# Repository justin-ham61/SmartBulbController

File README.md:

# SmartBulbController
SmartBulbController is an open-source input device built for the ESP32 microcontroller for controlling Smart Bulbs using the TP-Link Smart Home Protocol.

The goal of this project was to create a remote control device for Kasa Smart Lighting system within local network in order to eliminate the need for a smart phone app for lighting control.

# Dependencies
Several libraries are required for the device to work. 
- Adafruit_SSD1306 by Adafruit
- Adafruit_BusIO by Adafruit
- Adafruit_GFX_Library by Adafruit
- Ai_Esp32_Rotary_Encoder by Igor Antolic
- KasaSmartPlug updated by Justin Ham
    - Modified version of the [KasaSmartPlug](https://github.com/kj831ca/KasaSmartPlug?tab=readme-ov-file) library by Kris Jearakul to be compatible with Smart Bulbs and Smart Plugs.
- ArduinoJson by Benoit Blanchon

# Features
- Quick communication with light bulbs using the TP-Link Smart Home Protocol which is a TCP/IP Protocol that sends JSON payloads to devices. 
- Rotary Knob allows the control of brightness for multiple bulbs at the same time which is not available in the Kasa app.
- Built on FreeRTOS for efficient and responsive device interaction.
- OLED Display for bulb management and view of device states such as (On, Off, Error).

# FreeRTOS
- WiFi related tasks are managed using Semaphores and prohibits reliant tasks from running unless a connection is successfully made.
- User inputs are handled with ISR's that interact with RTOS queues.
- All tasks only operate when items are added to the queue and executes them promptly.
- Tasks notify lower priority tasks such as display task in order to update display.

# Designs

## Device Render
Device was designed with Fusion and prototype was printed using an Ender 3 Pro 3D Printer.

## First Working Prototype
First working prototype of the controller with a custom PCB and the 3D printed case.

## OLED Display
- Menu
    - List of all bulbs and a dedicated "Reset" command for the ESP32 microcontroller. 
        - Although the firmware has auto update for dynamic IP assignment, it may have issue updating to the most recent IP address of the bulb.
        - The reset button can be used to restart the device and connect to the new IP.
- Bulbs show the current state of the bulb 
    - On
    - Off
    - Error (Exclamation icon)
- Changing the brightness will show the current brightness as a progress bar.

## Inputs
- 2 Rotary Encoders
    - 1 Encoder for menu navigation
    - 1 Encoder for On/Off and brightness control
- 5 Switches (MX Style)
    - Quick toggle for individual bulbs
    
## Control Options
User can control their light bulbs in several different ways

1. Use the quick use rotary encoder
    - Press encoder button to toggle On/Off for all bulbs
    - Rotate encoder knob to change the brightness for all bulbs
2. Quck individual bulb toggle
    - The 5 switches allow the users to quickly turn on and off individual bulbs
3. Menu Select toggle
    - Navigate and select desired bulb on the menu in order to toggle and change the brightness of a specific bulb.  

# Set Up Guide

1. Gather all materials listed in the parts document, you can order the PCB using the provided files or wire the device with a breadboard following the schematics. 
2. Prepare config file before flashing the device (Instruction shown below).
3. Once the device is put together, flash the device with the firmware and required libraries using the Arduino IDE.
4. Device set up will run automatically on initial start up. 
    - This step includes the device searching for bulbs as outlined in the config file on the local wifi network.
    - Having the device connected to a computer and reading the Serial output will help with any connectivity issues. 
    - Notes about better connection below
5. Once set up, all lightbulbs named in the config file should show up on the main menu.
6. The first 5 lights can be toggled with the 5 switches.

## Config File Instruction
In order to flash the ESP32 module with the firmware, the user must update the config file with some information.
- Home Wifi SSID (name) and Password
- Names of all light bulbs they want
    - Name must match the name set for the bulb during set up exactly.
- Total number of bulbs
~~~c++
#ifndef CONFIG_H
#define CONFIG_H

const char* SSID = "<User WiFi SSID>";
const char* PASSWORD = "<User WiFi Password>";

//List of all user bulb names
char* aliases[] = {
  "<User Bulb Name 1>",
  "<User Bulb Name 2>",
  "<User Bulb Name 3>"
};

//Total number of bulbs, needs to match the number of bulb names above.
const int size = 0;

//Time between inactivity and sleep
const int inactivity_time = 15000;

//Minimum and Maximum brightness
const int min_brightness = 0;
const int max_brightness = 100;

#endif
~~~~

On start up, the ESP32 will begin to look for bulbs that are active and add them to the device's list of bulbs if the name is included in the config file.

For best results, please turn the smart bulb on with a phone during the set up.

# Future Plans
- Light temperature and color control.
- Custom group creations to group certain bulbs with another.
- Better rotary knob control between menu and controlling bulbs.
- Compatibility with devices that require Kasa Authentication such as light strips.

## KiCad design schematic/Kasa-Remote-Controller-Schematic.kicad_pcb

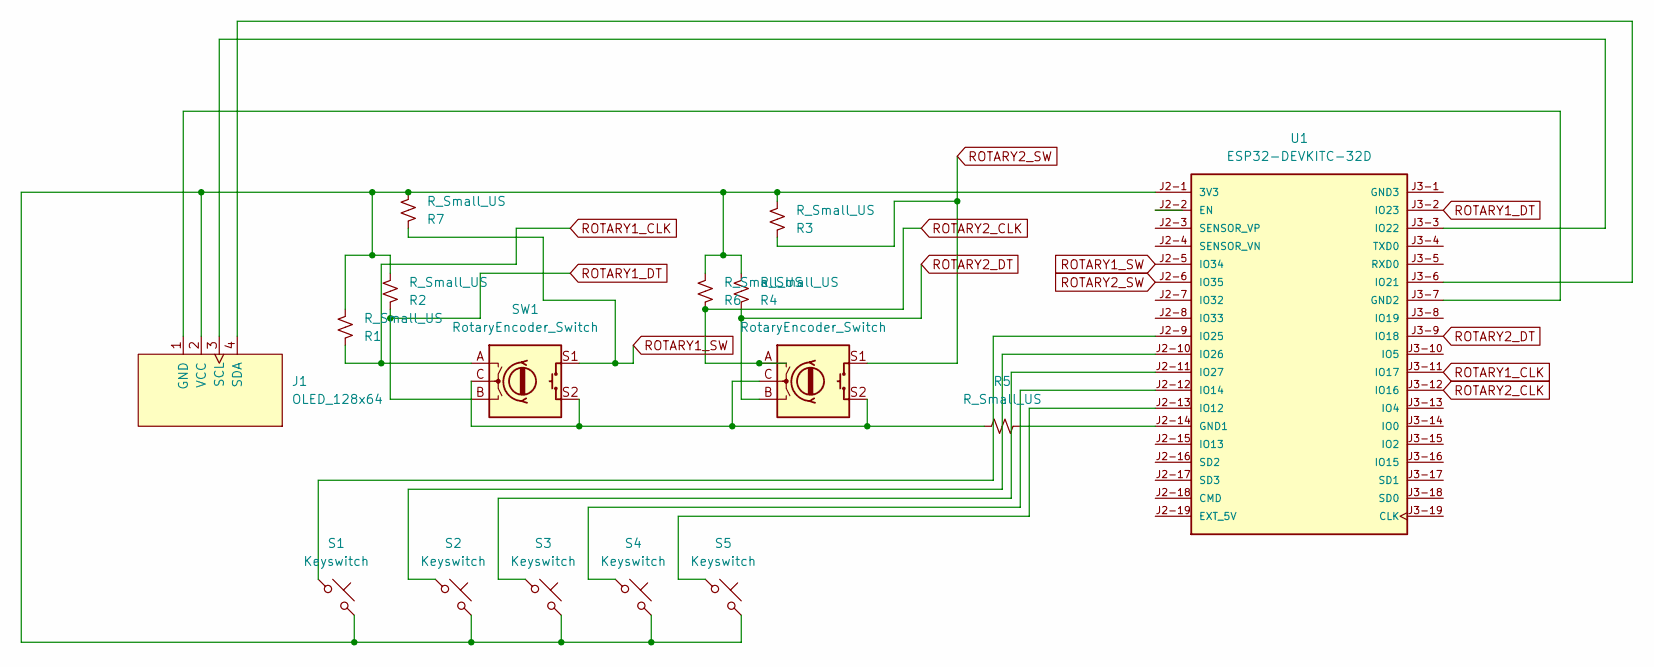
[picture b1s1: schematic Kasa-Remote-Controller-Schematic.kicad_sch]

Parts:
J1: OLED_128x64; MODULE_DM-OLED096-636
R1, R2, R3, R4, R5, R6, R7: R_Small_US; R_1206_3216Metric_Pad1.30x1.75mm_HandSolder
S1, S2, S3, S4, S5: Keyswitch; MX_PCB_1.00u
SW1, SW2: RotaryEncoder_Switch; RotaryEncoder_Alps_EC12E-Switch_Vertical_H20mm
U1: ESP32-DEVKITC-32D; MODULE_ESP32-DEVKITC-32D; PARTREV V4

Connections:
unnamed: J1.1 (GND), U1.J3-7 (GND2)
unnamed: J1.3 (SCL), U1.J3-3 (IO22)
unnamed: J1.4 (SDA), U1.J3-6 (IO21)
unnamed: J1.2 (VCC), R1.2, R2.2, R3.2, R4.2, R6.2, R7.2, S1.2, S2.2, S3.2, S4.2, S5.2, U1.J2-1 (3V3)
unnamed: R5.1, SW1.C, SW1.S2, SW2.C, SW2.S2
unnamed: R5.2, U1.J2-14 (GND1)
unnamed: S5.1, U1.J2-13 (IO12)
unnamed: S4.1, U1.J2-12 (IO14)
unnamed: S1.1, U1.J2-9 (IO25)
unnamed: S2.1, U1.J2-10 (IO26)
unnamed: S3.1, U1.J2-11 (IO27)
ROTARY1_CLK: R1.1, SW1.A, U1.J3-11 (IO17)
ROTARY1_DT: R2.1, SW1.B, U1.J3-2 (IO23)
ROTARY1_SW: R7.1, SW1.S1, U1.J2-5 (IO34)
ROTARY2_CLK: R6.1, SW2.A, U1.J3-12 (IO16)
ROTARY2_DT: R4.1, SW2.B, U1.J3-9 (IO18)
ROTARY2_SW: R3.1, SW2.S1, U1.J2-6 (IO35)

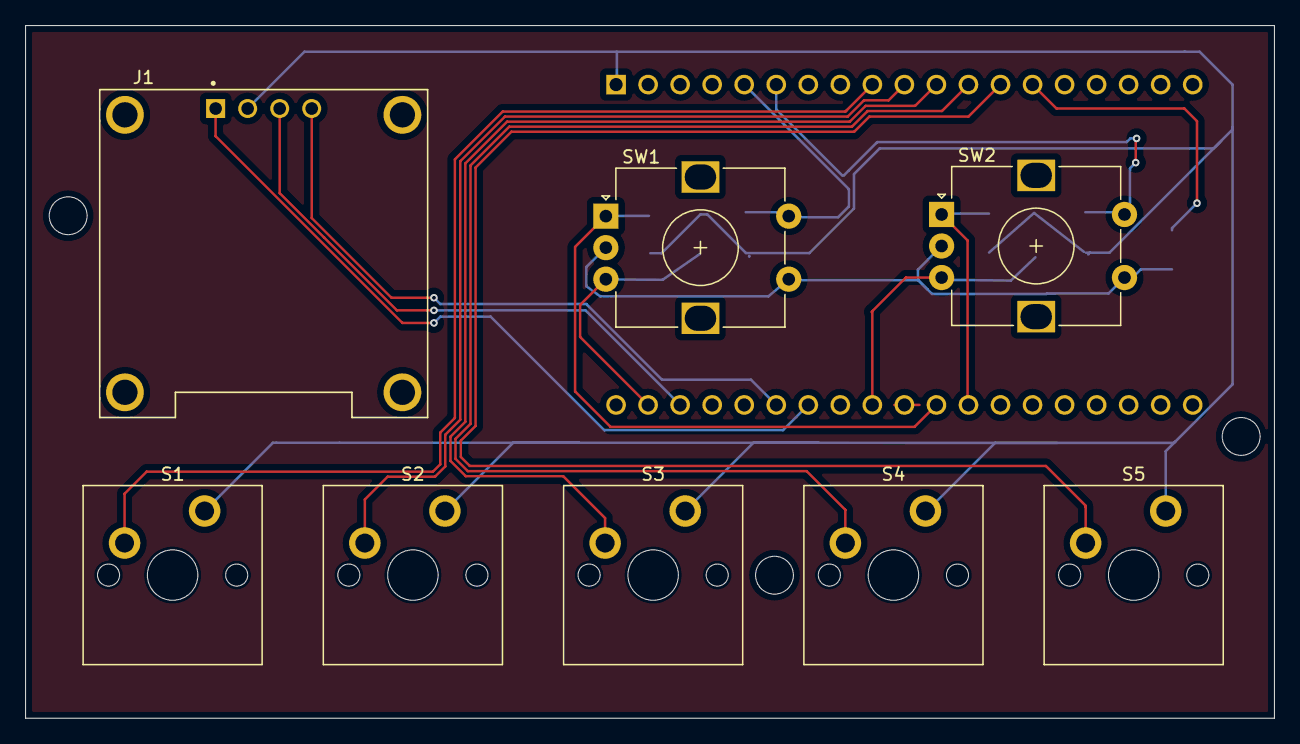
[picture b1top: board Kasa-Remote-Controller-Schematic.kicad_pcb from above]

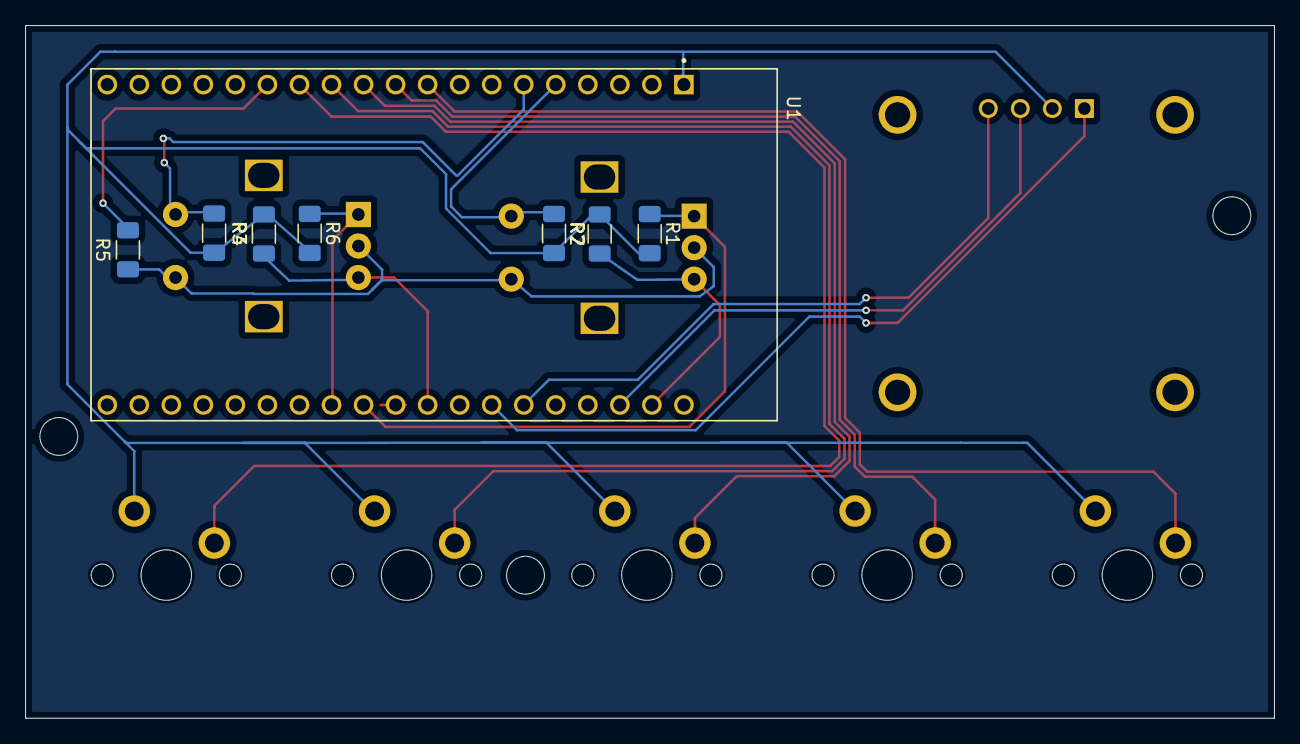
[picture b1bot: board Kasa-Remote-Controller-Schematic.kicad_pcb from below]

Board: 2 copper layers, 99.0 x 54.9 mm, 16 parts (8 on the bottom side), 17 nets.

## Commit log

2024-08-08 First commit of version 1 files
2024-08-08 Add parts spreadsheet
2024-08-08 updated library to be a copy
2024-08-08 removed reference to library git
2024-08-08 added KasaSmartDevice library source code
2024-08-08 Add README.md
2024-08-08 Add image to README.md
2024-08-08 Updat README.md
2024-08-09 Update image
2024-08-09 Revert image
2024-08-12 Add real life image
2024-08-12 Update README.md to have prototype image
2024-08-12 Update README.md description
2024-08-12 Update image sizes
2024-08-12 Added resized image
2024-08-12 Update README.md with resized image
2024-08-14 Update button state with bit operation and change button_loop to event driven loop
2024-08-14 clean up firmware
2024-08-26 Updated firmware with RTOS version
2024-09-03 update to most recent firmware
2025-01-14 separate tasks
